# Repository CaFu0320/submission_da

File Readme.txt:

Student Name: Carlos Funes

Student ID: 5007995832

Student Email: funesc2@unlv.nevada.edu

Primary Github Address: https://github.com/CaFu0320

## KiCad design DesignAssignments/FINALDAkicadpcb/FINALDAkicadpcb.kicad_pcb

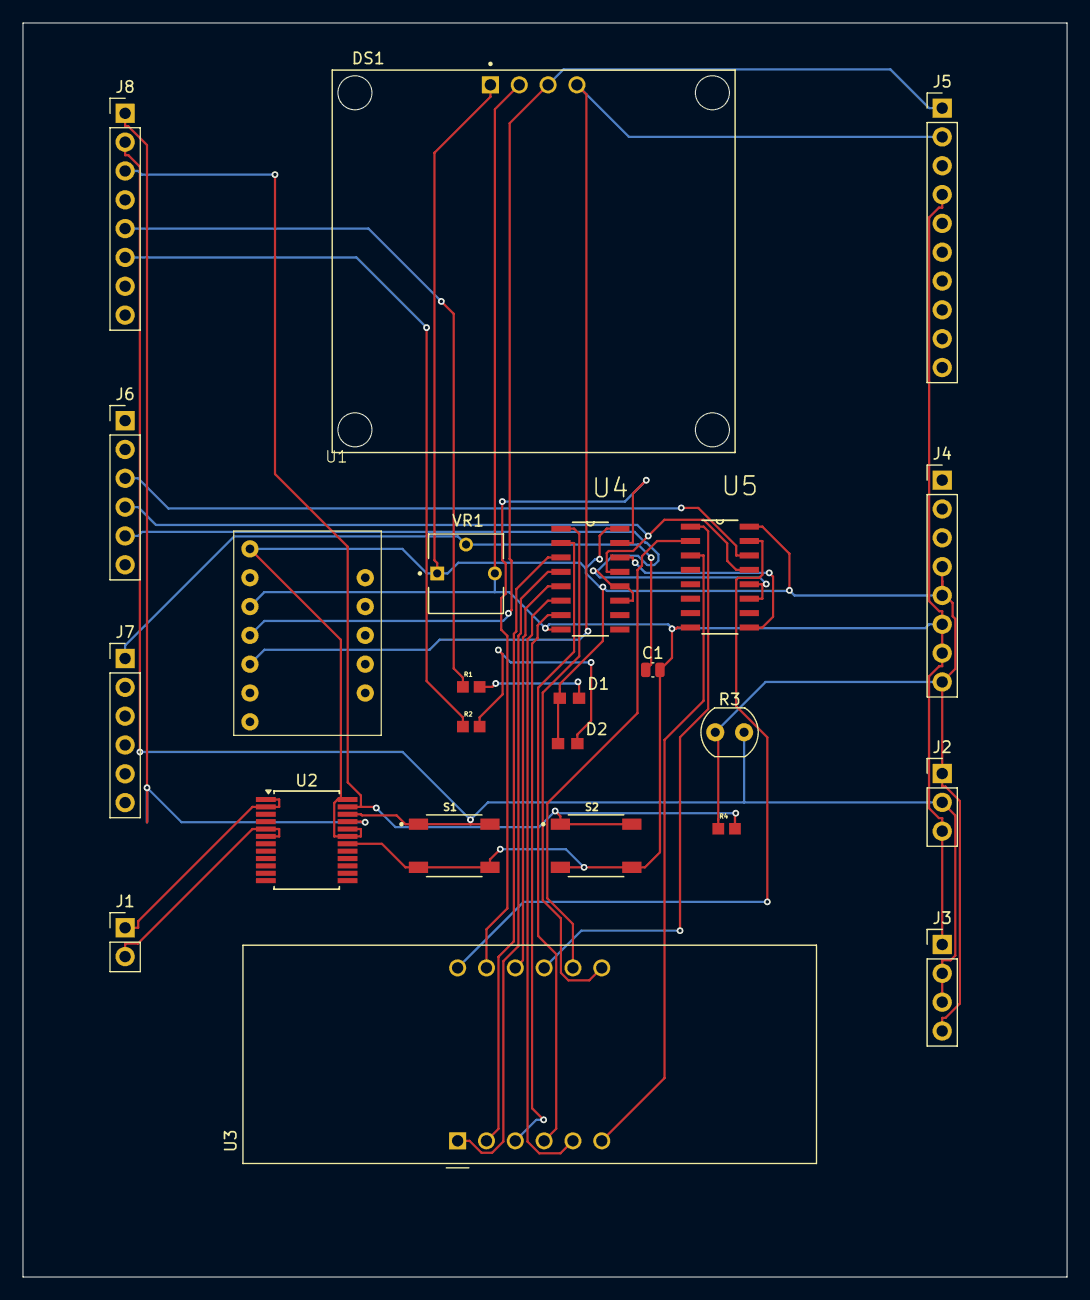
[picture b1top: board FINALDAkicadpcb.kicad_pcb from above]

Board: 2 copper layers, 92.0 x 110.5 mm, 24 parts (0 on the bottom side), 30 nets.

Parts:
C1: 1u; C_0504_1310Metric_Pad0.83x1.28mm_HandSolder
D1, D2: LTST-C193TGKT-5A; 0603
DS1: OLED_128X64_1.3_I2C; LCD_OLED_128X64_1.3_I2C
J1: Conn_01x02_Pin; PinHeader_1x02_P2.54mm_Vertical
J2: Conn_01x03_Pin; PinHeader_1x03_P2.54mm_Vertical
J3: Conn_01x04_Socket; PinHeader_1x04_P2.54mm_Vertical
J4, J8: Conn_01x08; PinHeader_1x08_P2.54mm_Vertical
J5: Conn_01x10; PinHeader_1x10_P2.54mm_Vertical
J6, J7: Conn_01x06; PinHeader_1x06_P2.54mm_Vertical
R1, R2: RC0603JR-071KL; RESC1607X60N
R3: 4.7k; R_LDR_4.9x4.2mm_P2.54mm_Vertical
R4: 4.7k; RESC1607X60N
S1, S2: 8-1437565-1; SW_8-1437565-1
U1: MODBMI160
U2: TB6612FNG; SSOP-24_5.3x8.2mm_P0.65mm
U3: CC56-12SRWA; CA56-12SRWA
U4, U5: 74HC595D_118; SOIC127P600X175-16N
VR1: 10k; TRIM_3362P-1-103LF

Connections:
3V3: D1.1, D2.1, DS1.1 (VDD), J2.1, J3.4, J4.4, J4.5, J4.8, R3.1, R4.1, U1.1 (VIN), U2.19 (STBY), U2.20 (VCC), U2.24 (VM1), U4.16 (VCC), U5.16 (VCC), VR1.1
DCMOT1: J1.1, U2.1 (AO1), U2.2 (AO1)
DCMOT2: J1.2, U2.5 (AO2), U2.6 (AO2)
GND: C1.2, DS1.2 (GND), J2.3, J3.1, J4.6, J4.7, J5.4, S1.3, S1.4, S2.3, S2.4, U1.3 (GND), U2.18 (GND), U4.8 (GND), U5.8 (GND), VR1.3
unnamed: D1.2, R1.2
unnamed: D2.2, R2.2
unnamed: U3.12 (CC1), U5.15 (Q0)
unnamed: U3.9 (CC2), U5.1 (Q1)
unnamed: U3.8 (CC3), U5.2 (Q2)
unnamed: U3.6 (CC4), U5.3 (Q3)
unnamed: U3.3 (DPX), U4.7 (Q7)
unnamed: U3.11 (a), U4.15 (Q0)
unnamed: U3.7 (b), U4.1 (Q1)
unnamed: U3.4 (c), U4.2 (Q2)
unnamed: U3.2 (d), U4.3 (Q3)
unnamed: U3.1 (e), U4.4 (Q4)
unnamed: U3.10 (f), U4.5 (Q5)
unnamed: U3.5 (g), U4.6 (Q6)
unnamed: U4.14 (DS), U5.9 (Q7_2)
PB3: J6.3, U5.14 (DS)
PB4: J6.4, U4.13 (~OE), U5.13 (~OE)
PB5: J6.5, U4.11 (SH_CP), U4.12 (ST_CP), U5.11 (SH_CP), U5.12 (ST_CP)
PC0: C1.1, J7.1, VR1.2
PC4: DS1.4 (SDA), J5.2, U1.5 (SDA)
PC5: DS1.3 (SCK), J5.1, U1.4 (SCL)
PD1: J8.1, U2.21 (AIN1)
PD2: J2.2, J3.2, J3.3, J8.2, R3.2, S1.1, S1.2, U2.22 (AIN2)
PD3: J8.3, R4.2, S2.1, S2.2, U2.23 (PWMA)
PD5: J8.5, R1.1
PD6: J8.6, R2.1

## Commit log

2025-02-24 Design Assignment 1 Upload
2025-03-23 DA2 Carlos Funes
2025-03-23 updated names
2025-03-23 da2pdf
2025-03-28 da 3 added
2025-03-29 word document added
2025-03-29 Rename text.txt to ignoreRDwordfilepls.txt
2025-03-29 Rename ignoreRDwordfilepls.txt to ignoreRDwordfileplease.txt
2025-04-07 DA4 ADDED
2025-04-07 DA 4 AND WORD DOCUMENT ADDED
